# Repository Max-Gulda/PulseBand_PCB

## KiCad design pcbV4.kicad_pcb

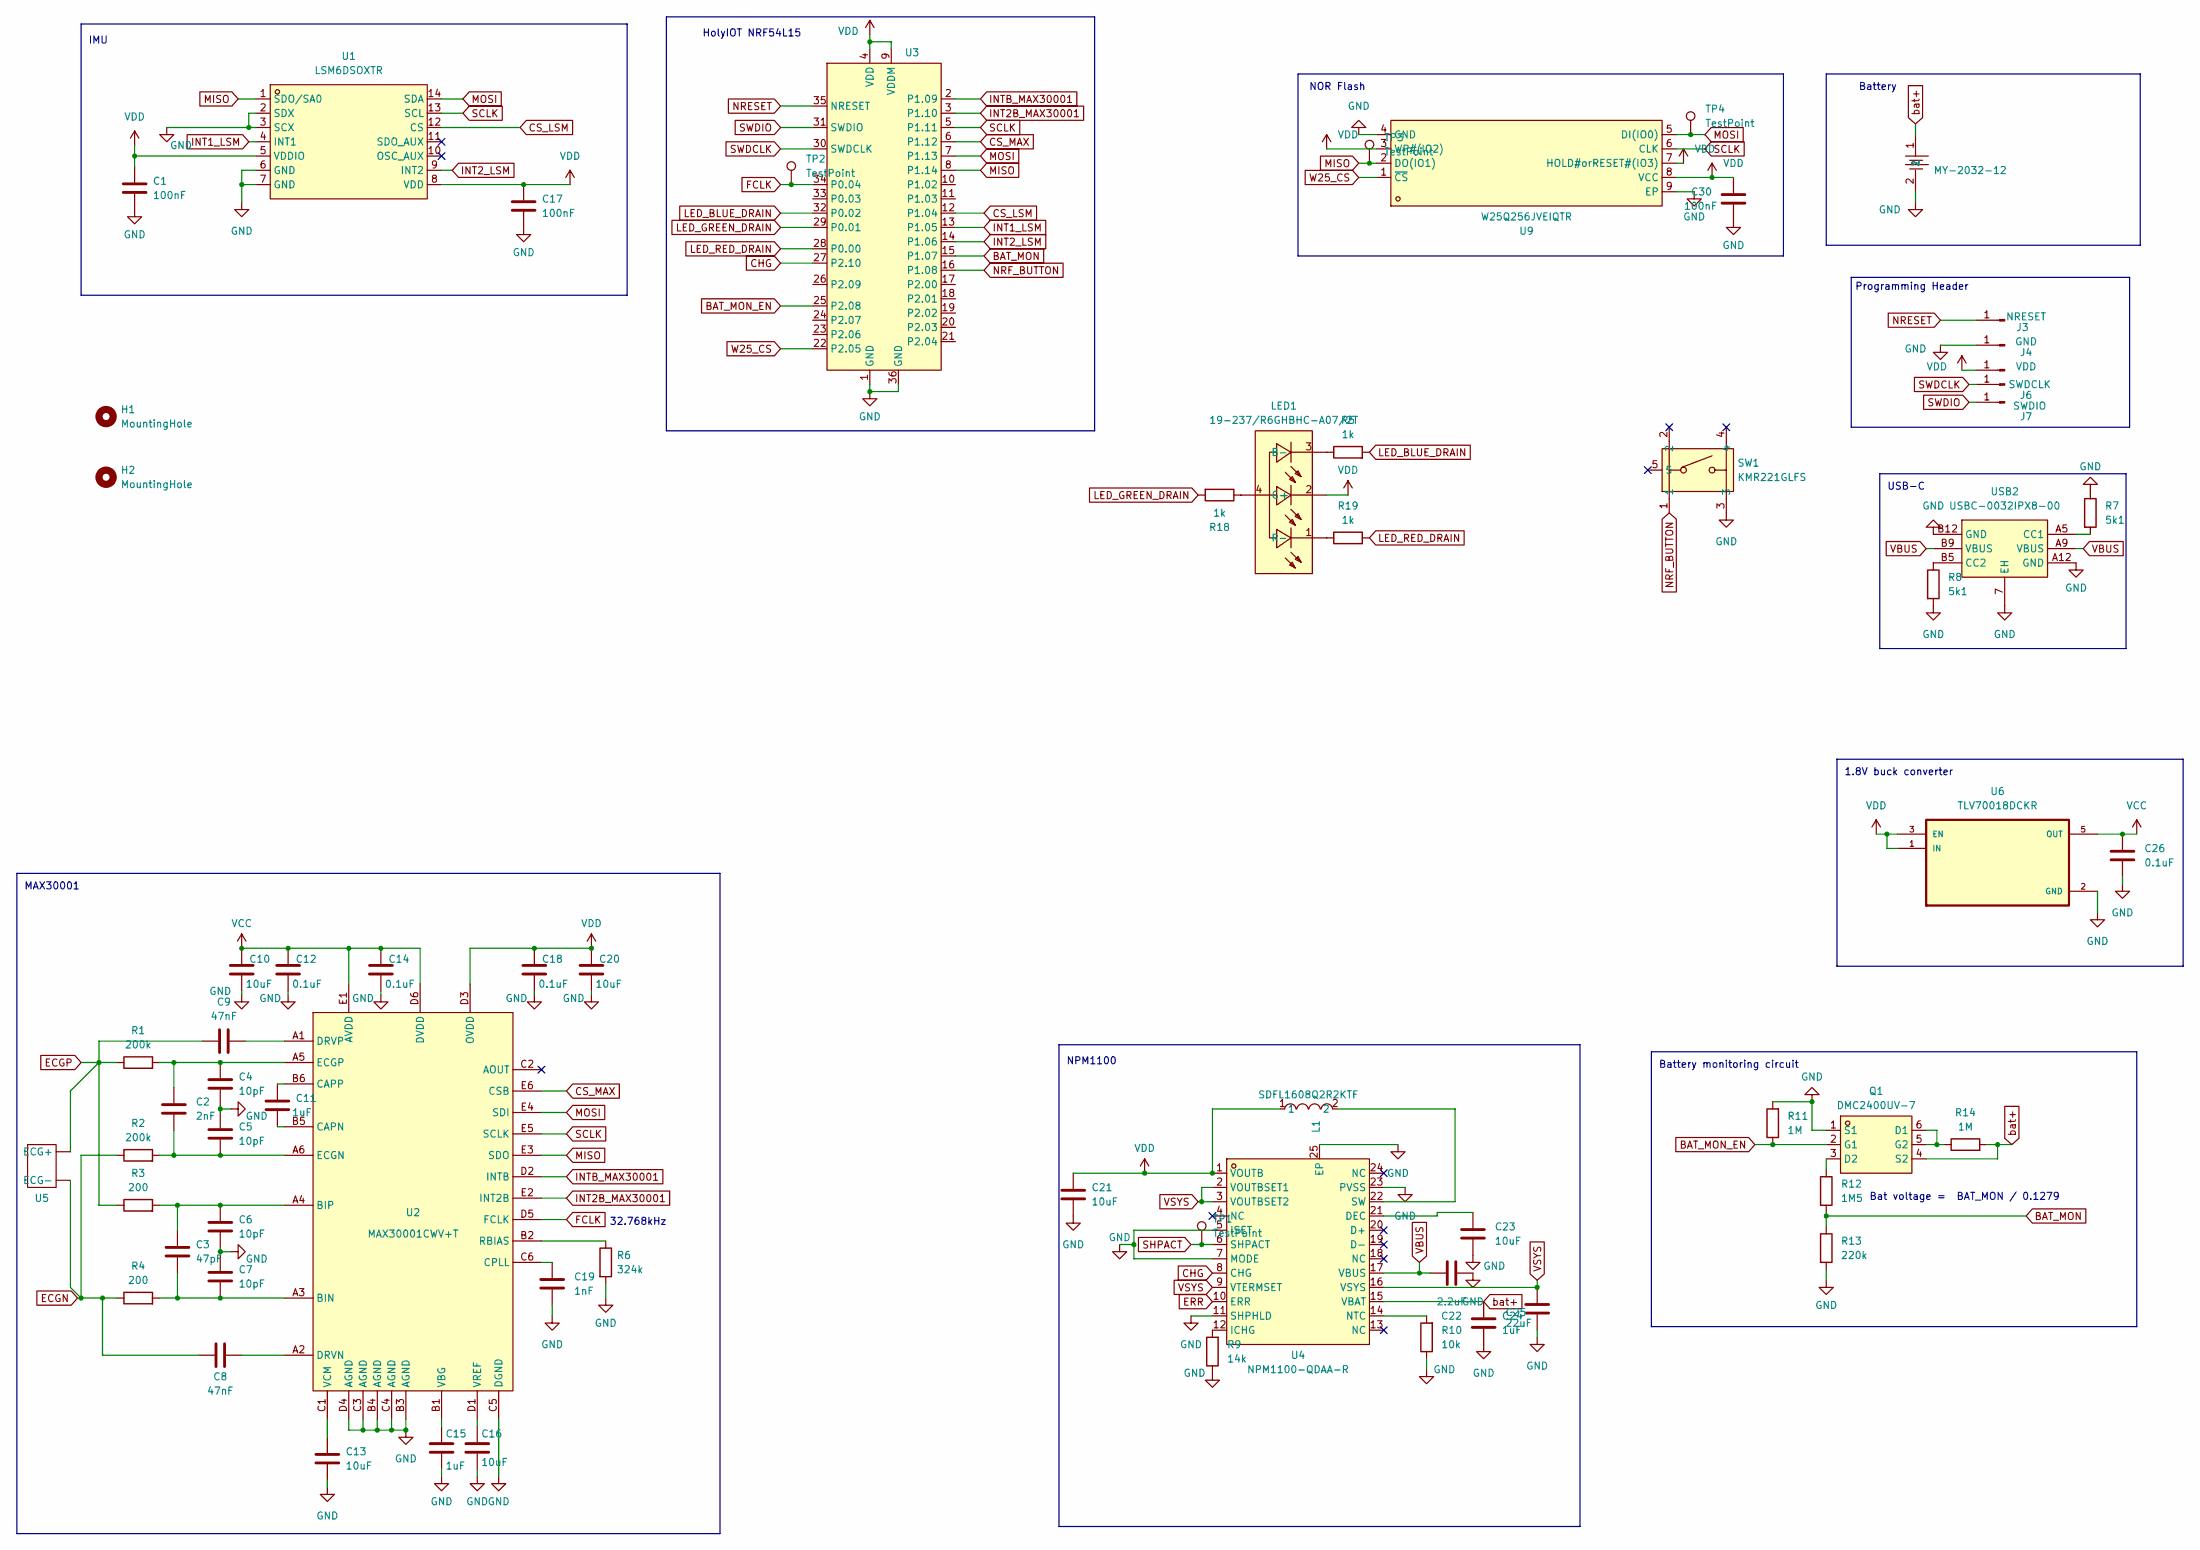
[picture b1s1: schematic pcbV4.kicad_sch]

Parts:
BT1: MY-2032-12; BAT-SMD_MY-2032-12; MPN MY-2032-12; LCSC Part C964833
C1, C17, C30: 100nF; C_0402_1005Metric
C2: 2nF; C_0402_1005Metric
C3: 47pF; C_0402_1005Metric
C4, C5, C6, C7: 10pF; C_0402_1005Metric
C8, C9: 47nF; C_0402_1005Metric
C10, C13, C16, C20, C21, C23: 10uF; C_0402_1005Metric
C11, C15, C24: 1uF; C_0402_1005Metric
C12, C14, C18, C26: 0.1uF; C_0402_1005Metric
C19: 1nF; C_0402_1005Metric
C22: 2.2uF; C_0402_1005Metric
C25: 22uF; C_0402_1005Metric
H1, H2: MountingHole; MountingHole_2.2mm_M2
J3: NRESET; SolderWirePad_1x01_SMD_1x2mm
J4: GND; SolderWirePad_1x01_SMD_1x2mm
J5: VDD; SolderWirePad_1x01_SMD_1x2mm
J6: SWDCLK; SolderWirePad_1x01_SMD_1x2mm
J7: SWDIO; SolderWirePad_1x01_SMD_1x2mm
L1: SDFL1608Q2R2KTF; L0603; LCSC Part C1033
LED1: 19-237/R6GHBHC-A07/2T; LED-ARRAY-SMD_4P-L1.6-W1.6-BL-CW; MPN 19-237/R6GHBHC-A07/2T; LCSC Part C264511
Q1: DMC2400UV-7; SOT-563_L1.6-W1.2-P0.50-LS1.6-BL; MPN DMC2400UV-7; LCSC Part C177025
R1, R2: 200k; R_0402_1005Metric
R3, R4: 200; R_0402_1005Metric
R5, R18, R19: 1k; R_0402_1005Metric
R6: 324k; R_0402_1005Metric
R7, R8: 5k1; R_0402_1005Metric
R9: 14k; R_0402_1005Metric
R10: 10k; R_0402_1005Metric
R11, R14: 1M; R_0402_1005Metric
R12: 1M5; R_0402_1005Metric
R13: 220k; R_0402_1005Metric
SW1: KMR221GLFS; KEY-SMD_KMR2XXGXXX; MPN KMR221GLFS; LCSC Part C72443
TP1, TP2, TP3, TP4: TestPoint; TestPoint_Pad_D1.5mm
U1: LSM6DSOXTR; LGA-14L_L3.0-W2.5-P0.50-TL; LCSC Part C481766
U2: MAX30001CWV+T; WLP-30_L2.7-W2.9-R5-C6-P0.50-TL; LCSC Part C2650384
U3: holyIOT
U4: NPM1100-QDAA-R; QFN-24_L4.0-W4.0-P0.50-TL-EP2.7; LCSC Part C5816773
U5: ECG connectors
U6: TLV70018DCKR; SOT65P210X110-5N
U9: W25Q256JVEIQTR; WSON-8_L8.0-W6.10-P1.27-BL-EP; MPN W25Q256JVEIQ; LCSC Part C97522
USB2: USBC-0032IPX8-00; TYPE-C-USB-SMD_USBC-0032IPX8-00; MPN USBC-0032IPX8-00; LCSC Part C783299

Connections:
BAT_MON: R12.2, R13.1, U3.15 (P1.07)
BAT_MON_EN: Q1.2 (G1), R11.1, U3.25 (P2.08)
CHG: U3.27 (P2.10), U4.8 (CHG)
CS_LSM: U1.12 (CS), U3.12 (P1.04)
CS_MAX: U2.E6 (CSB), U3.6 (P1.12)
ECGN: C8.1, R2.1, R4.1, U5.
ECGP: C9.1, R1.1, R3.1, U5.
ERR: U4.10 (ERR)
FCLK: TP2.1, U2.D5 (FCLK), U3.34 (P0.04)
GND: BT1.2, C1.2, C4.2, C5.1, C6.2, C7.1, C10.2, C12.2, C13.2, C14.2, C15.2, C16.2, C17.2, C18.2, C19.2, C20.2, C21.2, C22.1, C23.2, C24.2, C25.2, C26.2, C30.2, J4.1, Q1.1 (S1), R6.2, R7.1, R8.2, R9.1, R10.1, R11.2, R13.2, SW1.3, U1.2 (SDX), U1.3 (SCX), U1.6 (GND), U1.7 (GND), U2.B3 (AGND), U2.B4 (AGND), U2.C3 (AGND), U2.C4 (AGND), U2.C5 (DGND), U2.D4 (AGND), U3.1 (GND), U3.36 (GND), U4.5 (ISET), U4.7 (MODE), U4.11 (SHPHLD), U4.23 (PVSS), U4.25 (EP), U6.2 (GND), U9.4 (GND), U9.9 (EP), USB2.7 (EH), USB2.A12 (GND), USB2.B12 (GND)
INT1_LSM: U1.4 (INT1), U3.13 (P1.05)
INT2B_MAX30001: U2.E2 (INT2B), U3.3 (P1.10)
INT2_LSM: U1.9 (INT2), U3.14 (P1.06)
INTB_MAX30001: U2.D2 (INTB), U3.2 (P1.09)
LED_BLUE_DRAIN: R5.2, U3.32 (P0.02)
LED_GREEN_DRAIN: R18.2, U3.29 (P0.01)
LED_RED_DRAIN: R19.2, U3.28 (P0.00)
MISO: TP3.1, U1.1 (SDO/SA0), U2.E3 (SDO), U3.8 (P1.14), U9.2 (DO(IO1))
MOSI: TP4.1, U1.14 (SDA), U2.E4 (SDI), U3.7 (P1.13), U9.5 (DI(IO0))
NRESET: J3.1, U3.35 (NRESET)
NRF_BUTTON: SW1.1, U3.16 (P1.08)
unnamed: LED1.4 (+), R18.1
unnamed: LED1.3 (B-), R5.1
unnamed: LED1.1 (R-), R19.1
unnamed: Q1.5 (G2), Q1.6 (D1), R14.1
unnamed: Q1.3 (D2), R12.1
unnamed: C3.2, C7.2, R4.2, U2.A3 (BIN)
unnamed: C3.1, C6.1, R3.2, U2.A4 (BIP)
unnamed: C11.2, U2.B5 (CAPN)
unnamed: C11.1, U2.B6 (CAPP)
unnamed: C19.1, U2.C6 (CPLL)
unnamed: C8.2, U2.A2 (DRVN)
unnamed: C9.2, U2.A1 (DRVP)
unnamed: C2.2, C5.2, R2.2, U2.A6 (ECGN)
unnamed: C2.1, C4.1, R1.2, U2.A5 (ECGP)
unnamed: R6.1, U2.B2 (RBIAS)
unnamed: C15.1, U2.B1 (VBG)
unnamed: C13.1, U2.C1 (VCM)
unnamed: C16.1, U2.D1 (VREF)
unnamed: C23.1, U4.21 (DEC)
unnamed: R9.2, U4.12 (ICHG)
unnamed: R10.2, U4.14 (NTC)
unnamed: L1.2, U4.22 (SW)
unnamed: R7.2, USB2.A5 (CC1)
unnamed: R8.1, USB2.B5 (CC2)
SCLK: U1.13 (SCL), U2.E5 (SCLK), U3.5 (P1.11), U9.6 (CLK)
SHPACT: TP1.1, U4.6 (SHPACT)
SWDCLK: J6.1, U3.30 (SWDCLK)
SWDIO: J7.1, U3.31 (SWDIO)
VBUS: C22.2, U4.17 (VBUS), USB2.A9 (VBUS), USB2.B9 (VBUS)
VCC: C10.1, C12.1, C14.1, C26.1, U2.D6 (DVDD), U2.E1 (AVDD), U6.5 (OUT)
VDD: C1.1, C17.1, C18.1, C20.1, C21.1, C30.1, J5.1, L1.1, LED1.2 (G-), U1.5 (VDDIO), U1.8 (VDD), U2.D3 (OVDD), U3.4 (VDD), U3.9 (VDDM), U4.1 (VOUTB), U6.1 (IN), U6.3 (EN), U9.3 (WP#(IO2)), U9.7 (HOLD#orRESET#(IO3)), U9.8 (VCC)
VSYS: C25.1, U4.2 (VOUTBSET1), U4.3 (VOUTBSET2), U4.9 (VTERMSET), U4.16 (VSYS)
W25_CS: U3.22 (P2.05), U9.1 (~CS)
bat+: BT1.1, C24.1, Q1.4 (S2), R14.2, U4.15 (VBAT)

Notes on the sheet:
MAX30001
NOR Flash
32.768kHz
Bat voltage = BAT_MON / 0.1279
1.8V buck converter
HolyIOT NRF54L15
NPM1100
Programming Header
IMU
Battery
Battery monitoring circuit
USB-C

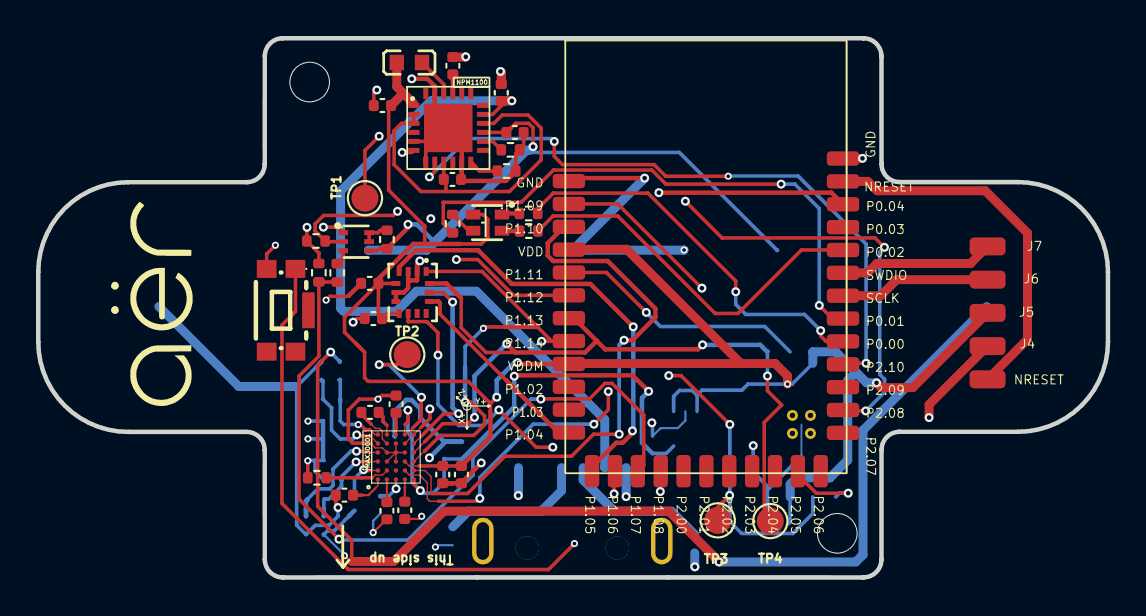
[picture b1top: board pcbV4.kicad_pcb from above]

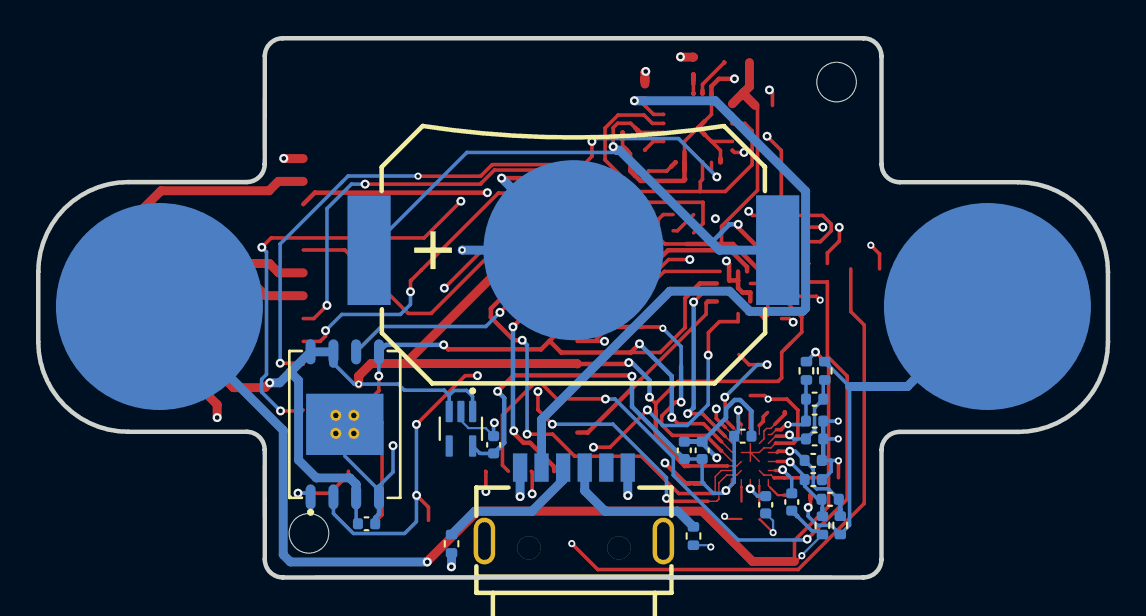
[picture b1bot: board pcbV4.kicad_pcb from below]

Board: 4 copper layers, 59.4 x 30.0 mm, 66 parts (23 on the bottom side), 54 nets.

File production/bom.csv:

Designator,Footprint,Quantity,Value,LCSC Part #
BT1,BAT-SMD_MY-2032-12,1,MY-2032-12,C964833
BTN,KEY-SMD_KMR2XXGXXX,1,KMR221GLFS,C72443
"C1, C17, C30",0402,3,100nF,
"C10, C13, C16, C20, C21, C23",0402,6,10uF,
"C11, C15, C24",0402,3,1uF,
"C12, C14, C18, C26",0402,4,0.1uF,
C19,0402,1,1nF,
C2,0402,1,2nF,
C22,0402,1,2.2uF,
C25,0402,1,22uF,
C3,0402,1,47pF,
"C4, C5, C6, C7",0402,4,10pF,
"C8, C9",0402,2,47nF,
"FCLK, MISO, MOSI, SHPACT",TestPoint_Pad_D1.5mm,4,TestPoint,
GND,SolderWirePad_1x01_SMD_1x2mm,1,GND,
"H1, H2",MountingHole_2.2mm_M2,2,MountingHole,
J3,SolderWirePad_1x01_SMD_1x2mm,1,NRESET,
L1,L0603,1,SDFL1608Q2R2KTF,C1033
LED1,LED-ARRAY-SMD_4P-L1.6-W1.6-BL-CW,1,19-237/R6GHBHC-A07/2T,C264511
Q1,SOT-563_L1.6-W1.2-P0.50-LS1.6-BL,1,DMC2400UV-7,C177025
"R1, R2",0402,2,200k,
R10,0402,1,10k,
"R11, R14",0402,2,1M,
R12,0402,1,1M5,
R13,0402,1,220k,
"R18, R19, R5",0402,3,1k,
"R3, R4",0402,2,200,
R6,0402,1,324k,
"R7, R8",0402,2,5k1,
R9,0402,1,14k,
SCLK,SolderWirePad_1x01_SMD_1x2mm,1,SWDCLK,
SWDIO,SolderWirePad_1x01_SMD_1x2mm,1,SWDIO,
U1,LGA-14L_L3.0-W2.5-P0.50-TL,1,LSM6DSOXTR,C481766
U2,WLP-30_L2.7-W2.9-R5-C6-P0.50-TL,1,MAX30001CWV+T,C2650384
U3,holyIOT,1,~,
U4,QFN-24_L4.0-W4.0-P0.50-TL-EP2.7,1,NPM1100-QDAA-R,C5816773
U6,SOT65P210X110-5N,1,TLV70018DCKR,
U9,WSON-8_L8.0-W6.10-P1.27-BL-EP,1,W25Q256JVEIQTR,C97522
USB2,TYPE-C-USB-SMD_USBC-0032IPX8-00,1,USBC-0032IPX8-00,C783299
VDD,SolderWirePad_1x01_SMD_1x2mm,1,VDD,

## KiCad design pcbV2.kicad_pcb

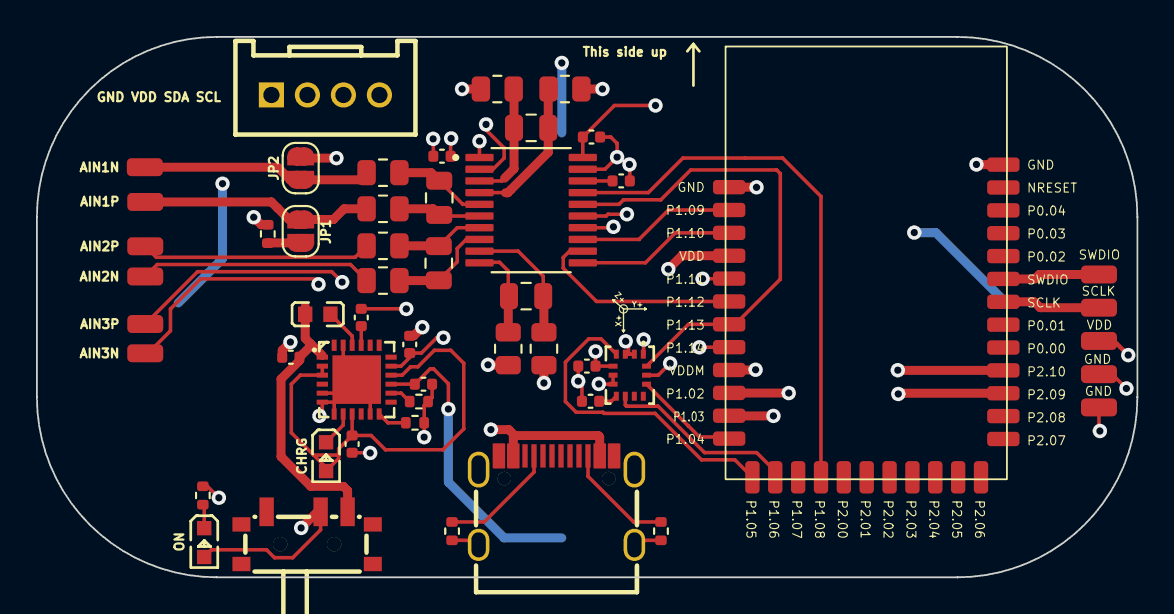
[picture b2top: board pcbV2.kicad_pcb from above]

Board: 4 copper layers, 61.1 x 30.0 mm, 52 parts (1 on the bottom side), 46 nets.

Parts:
AIN1N: Breathing-; SolderWirePad_1x01_SMD_1x2mm
AIN1P: Breathing+; SolderWirePad_1x01_SMD_1x2mm
AIN2N: AIN2N; SolderWirePad_1x01_SMD_1x2mm
AIN2P: AIN2P; SolderWirePad_1x01_SMD_1x2mm
AIN3N: AIN3N; SolderWirePad_1x01_SMD_1x2mm
AIN3P: AIN3P; SolderWirePad_1x01_SMD_1x2mm
C1, C2: 100nF; C_0402_1005Metric
C3: 220nF; C_0402_1005Metric
C4, C5, C8: 1uF; C_0402_1005Metric
C6, C10: 10uF; C_0402_1005Metric
C7: 2.2uF; C_0402_1005Metric
C9: 22uF; C_0402_1005Metric
C11: 20uF; C_0805_2012Metric
C12: 1.6uF; C_0805_2012Metric
C14, C15: 10nF; C_0805_2012Metric
CN1: SEEED-110990030; CONN-TH_SEEED-110990030
GND: GND; SolderWirePad_1x01_SMD_1x2mm
J5: GND; SolderWirePad_1x01_SMD_1x2mm
JP1, JP2: SolderJumper_2_Open; SolderJumper-2_P1.3mm_Open_RoundedPad1.0x1.5mm
L1: SDFL1608Q2R2KTF; L0603
LED1, LED3: Blue light 0603; LED0603-RD
R1: 2k; R_0402_1005Metric
R2, R3, R4, R5, R13, R14, R15, R16: 1k; R_0805_2012Metric
R6: 4k7; R_0402_1005Metric
R7, R8: 5k1; R_0402_1005Metric
R9: 1k5; R_0402_1005Metric
R10: 10k; R_0402_1005Metric
SCLK: SWDCLK; SolderWirePad_1x01_SMD_1x2mm
SW1: XDMK-12C01-25; SW-SMD_XDMK-12C01-25
SWDIO: SWDIO; SolderWirePad_1x01_SMD_1x2mm
U1: holyIOT
U2: ADS131M04IPWR; SOP65P640X120-20N
U3: NPM1100-QDAA-R; QFN-24_L4.0-W4.0-P0.50-TL-EP2.7
U4: LSM6DSOXTR; LGA-14L_L3.0-W2.5-P0.50-TL
U5: BS-08-B2AA020-R; BAT-SMD_BS-08-B2AA016
USBC1: TYPE-C-31-M-12; USB-C_SMD-TYPE-C-31-M-12_1
VDD: VDD; SolderWirePad_1x01_SMD_1x2mm

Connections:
AIN1N: C11.2, R3.2, U2.5 (AIN1N)
AIN1P: C11.1, R2.2, U2.6 (AIN1P)
AIN2N: C14.2, R14.2, U2.8 (AIN2N)
AIN2P: C14.1, R13.2, U2.7 (AIN2P)
AIN3N: C15.2, R16.2, U2.9 (AIN3N)
AIN3P: C15.1, R15.2, U2.10 (AIN3P)
CHG: LED3.1 (K), U3.8 (CHG)
CLKIN: U1.16 (P1.08), U2.17 (CLKIN)
CS: U1.6 (P1.12), U2.12 (~CS)
CS_LSM: U1.12 (P1.04), U4.12 (CS)
DIN: U1.7 (P1.13), U2.16 (DIN), U4.14 (SDA)
DOUT: U1.8 (P1.14), U2.15 (DOUT), U4.1 (SDO/SA0)
DRDY: U1.2 (P1.09), U2.13 (~DRDY)
ECG +: C12.1, R4.2, U2.3 (AIN0P)
ECG -: C12.2, R5.2, U2.4 (AIN0N)
GND_BRIDGE: JP2.1 (A), U1.27 (P2.10)
INT1_LSM: U1.13 (P1.05), U4.4 (INT1)
INT2_LSM: U1.14 (P1.06), U4.9 (INT2)
unnamed: AIN1P.1, JP1.1 (A), R2.1
unnamed: AIN1N.1, JP2.2 (B), R3.1
unnamed: AIN2P.1, R13.1
unnamed: AIN2N.1, R14.1
unnamed: AIN3P.1, R15.1
unnamed: AIN3N.1, R16.1
unnamed: JP1.2 (B), R1.2
unnamed: LED1.1 (K), R6.1
unnamed: C3.1, U2.18 (CAP)
unnamed: C10.1, U3.21 (DEC)
unnamed: R9.2, U3.12 (ICHG)
unnamed: R10.2, U3.14 (NTC)
unnamed: L1.2, U3.22 (SW)
unnamed: R7.1, USBC1.A5 (CC1)
unnamed: R8.1, USBC1.B5 (CC2)
SCL: CN1.4, U1.11 (P1.03)
SCLK: U1.5 (P1.11), U2.14 (SCLK), U4.13 (SCL)
SDA: CN1.3, U1.10 (P1.02)
SWDCLK: SCLK.1, U1.30 (SWDCLK)
SWDIO: SWDIO.1, U1.31 (SWDIO)
SYNC/RESET: U1.3 (P1.10), U2.11 (~SYNC/~RESET)
VBUS: C7.2, U3.17 (VBUS), USBC1.A4B9 (VBUS), USBC1.B4A9 (VBUS)
VCC_BRIDGE: R1.1, U1.26 (P2.09)
VDD: C1.1, C2.1, C4.1, C5.1, CN1.2, LED1.2 (A), SW1.2, U1.4 (VDD), U1.9 (VDDM), U2.1 (AVDD), U2.20 (DVDD), U4.5 (VDDIO), U4.8 (VDD), VDD.1
VOUT: C6.1, L1.1, SW1.1, U3.1 (VOUTB)
VSYS: C9.1, LED3.2 (A), U3.2 (VOUTBSET1), U3.3 (VOUTBSET2), U3.9 (VTERMSET), U3.16 (VSYS)
bat+: C8.1, U3.15 (VBAT), U5.1
bat-: C1.2, C2.2, C3.2, C4.2, C5.2, C6.2, C7.1, C8.2, C9.2, C10.2, CN1.1, GND.1, J5.1, R6.2, R7.2, R8.2, R9.1, R10.1, U1.1 (GND), U1.36 (GND), U2.2 (AGND), U2.19 (DGND), U3.5 (ISET), U3.6 (SHPACT), U3.7 (MODE), U3.11 (SHPHLD), U3.23 (PVSS), U3.25 (EP), U4.2 (SDX), U4.3 (SCX), U4.6 (GND), U4.7 (GND), U5.2, USBC1.1 (EH), USBC1.2 (EH), USBC1.3 (EH), USBC1.4 (EH), USBC1.A1B12 (GND), USBC1.B1A12 (GND)

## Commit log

2026-04-28 Add pcbV4 KiCad project
2026-04-28 Ignore KiCad generated backup files
2026-04-28 Update pcbV4 schematic
2026-04-29 Update pcbV4 KiCad design
2026-05-11 Update PCB production outputs
2026-05-15 kicad
2026-05-21 Deleted autosave files kicad
2026-05-28 Update PCB design
